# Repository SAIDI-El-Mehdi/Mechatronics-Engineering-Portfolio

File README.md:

# Mechatronics-Engineering-Portfolio
Academic projects and labs at ENSA Agadir.

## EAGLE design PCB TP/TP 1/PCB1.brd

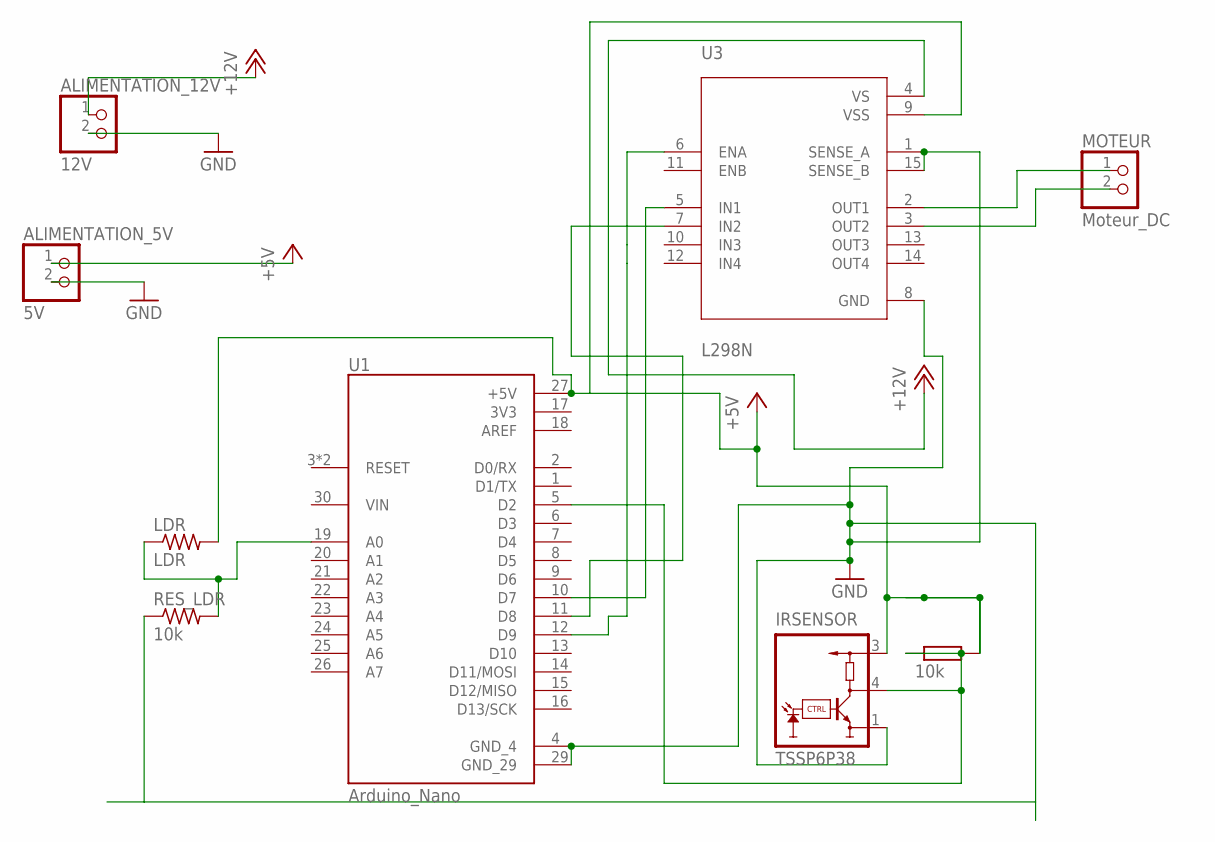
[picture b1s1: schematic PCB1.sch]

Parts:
ALIMENTATION_5V: 5V; 1X02
ALIMENTATION_12V: 12V; 1X02
IRSENSOR: TSSP6P38
LDR: LDR; WSC01/2
MOTEUR: Moteur_DC; 1X02
RES_LDR: 10k; 0204/5
R_PULL_UP: 10k; 0204V
U1: Arduino_Nano; MODULE_ARDUINO_NANO
U3: L298N; TO127P2020X500X2100-15

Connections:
+5V: ALIMENTATION_5V.1, IRSENSOR.3 (VS), LDR.2, R_PULL_UP.2, U1.27 (+5V), U3.9 (VSS)
+12V: ALIMENTATION_12V.1, U3.4 (VS)
GND: ALIMENTATION_5V.2, ALIMENTATION_12V.2, IRSENSOR.1 (GND), RES_LDR.1, U1.4 (GND_4), U1.29 (GND_29), U3.1 (SENSE_A), U3.8 (GND), U3.15 (SENSE_B)
IR_OUT: IRSENSOR.4 (OUT), R_PULL_UP.1, U1.5 (D2)
L298_ENA: U1.12 (D9), U3.6 (ENA)
L298_IN1: U1.10 (D7), U3.5 (IN1)
L298_IN2: U1.11 (D8), U3.7 (IN2)
LDR_SIGNAL: LDR.1, RES_LDR.2, U1.19 (A0)
MOTOR_OUT1: MOTEUR.1, U3.2 (OUT1)
MOTOR_OUT2: MOTEUR.2, U3.3 (OUT2)

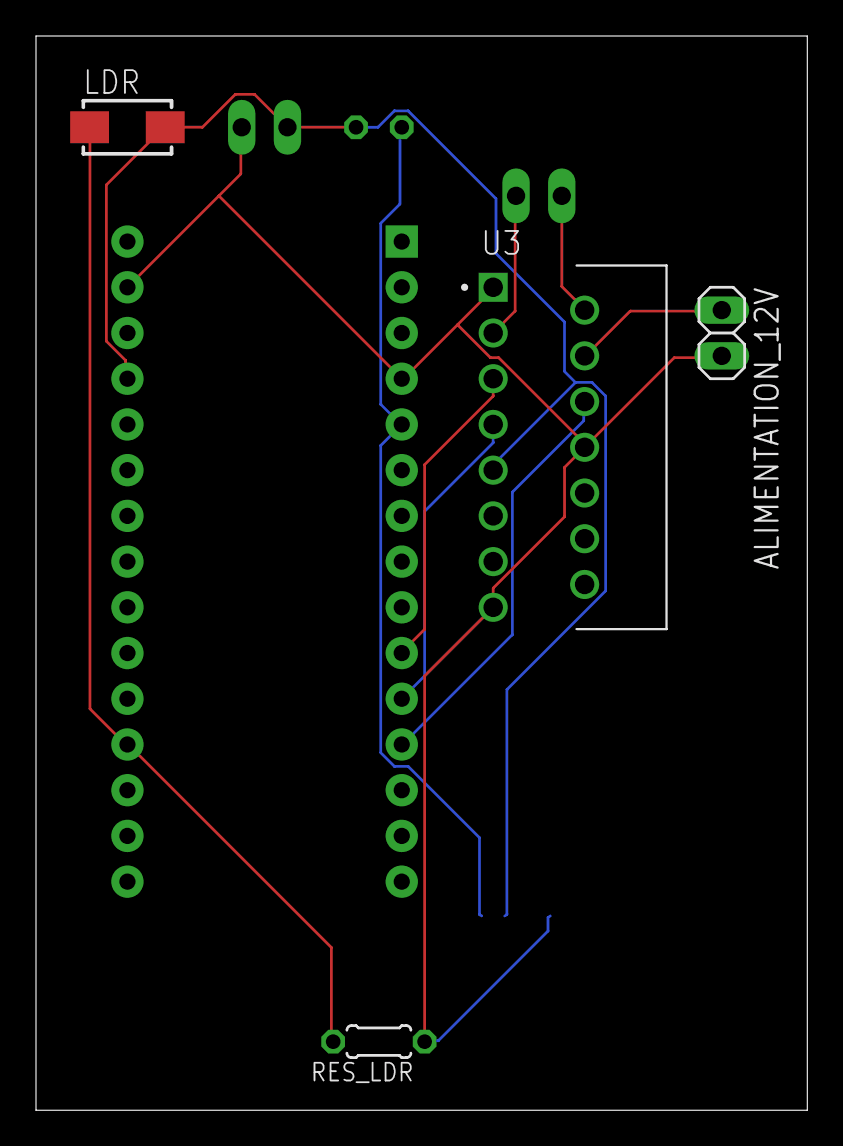
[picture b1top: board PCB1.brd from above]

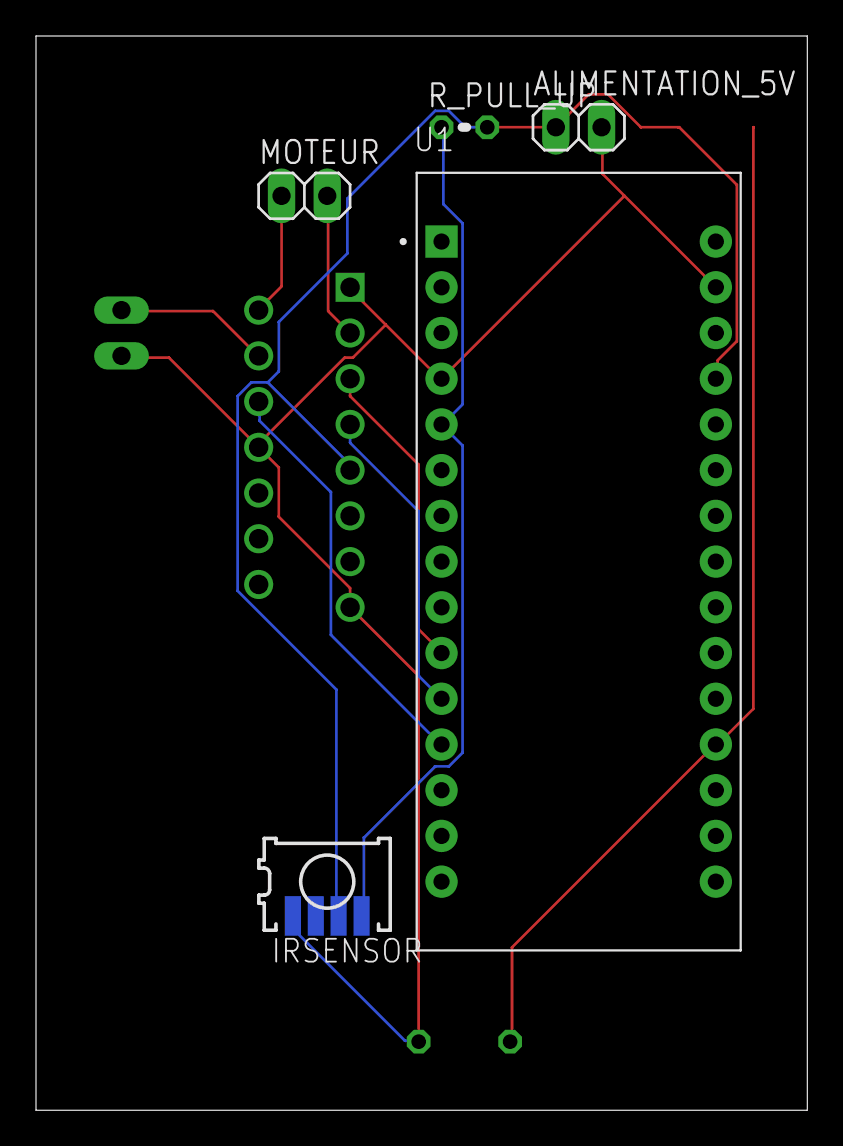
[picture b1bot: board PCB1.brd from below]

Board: 2 copper layers, 42.9 x 59.7 mm, 9 parts (5 on the bottom side), 10 nets.

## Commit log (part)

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2025-12-16 Create README.md
    Projects for Embedded Systems
2025-12-16 Create README.md
    Smart Traffic Light Controller (VHDL)
    Implemented on FPGA (Cyclone/Altera) using VHDL.
    Features:
    - Finite State Machine (FSM) for traffic logic.
    - Automatic and Manual modes.
2025-12-16 Add VHDL Smart Traffic Light Controller
    Uploaded structural architecture files, testbench, and Quartus project settings.
2025-12-16 Create README.md
    3-to-8 LED Decoder (VHDL)
    Simple combinatorial logic to control 8 LEDs using 3 switches (Case statement).
2025-12-16 Add VHDL code for 3-to-8 Decoder
    LED-Decoder-3to8
2025-12-16 Create README.md
    4-Bit Binary Adder with 7-Segment Display
    Structural VHDL implementation of a 4-bit Full Adder using 1-bit adder components.
    Features:
    - 4-bit addition using structural architecture.
    - Binary to BCD conversion.
    - Output display on 7-Segment HEX (Units and Tens).
2025-12-16 Add structural 4-bit adder with BCD display
2025-12-16 Create README.md
    Modulo-N Counter with 7-Segment Display
    A flexible counter that counts up to a user-defined value 'N'.
    Features:
    - User-defined Modulo limit (input N).
    - Clock Divider for visible counting speed (1Hz approx).
    - Dynamic display on 7-Segment HEX displays.
2025-12-16 dd Modulo-N counter with display controller
2025-12-16 Create README.md
    # Gear Train Mechanism (DMU Kinematics)
    3D Modeling and Kinematic simulation of a gear train system using CATIA V5.
    ## 📸 Design Preview
    ![Gear Assembly Render](./render_gears.png)
    ## ⚙️ Features
    - Parametric gear design.
2025-12-16 Gear-Train-DMU.
2025-12-16 Create README.md
    # Scotch Yoke Mechanism (Transformation de Mouvement)
    A kinematic simulation of a Scotch Yoke mechanism designed in CATIA V5.
    This mechanism converts rotational motion into linear reciprocating motion.
    ## 📸 Project Gallery
    Here is the 3D Isometric view and the Assembly Tree structure:
    ![3D Render](./render_iso.png)
2025-12-16 Scotch-Yoke-Mechanism
    # Scotch Yoke Mechanism (Transformation de Mouvement)
    A kinematic simulation of a Scotch Yoke mechanism designed in CATIA V5.
    This mechanism converts rotational motion into linear reciprocating motion.
    ## 📸 Project Gallery
    Here is the 3D Isometric view and the Assembly Tree structure:
    ![3D Render](./render_iso.png)
2025-12-16 Update README.md
    ## 📸 Project Gallery
    Here is the 3D Isometric view and the Assembly Tree structure:
    ![3D Render](./render_iso.png.jpg)
    ![Design Tree](./design_tree.jpg.png)
2025-12-16 Axe-Galet-Assembly
2025-12-16 Create README.md
    # Agricultural Tractor Design (Tracteur Agricole)
    A detailed 3D model of an agricultural tractor designed in CATIA V5.
    This project demonstrates complex **Part Design** and multi-body modeling techniques.
    ## 📸 Design Views
    Here are the Isometric, Top, Side, and Front views of the tractor:
    ![Tractor Views](./tractor_views.jpg)
2025-12-16 TRACTOR.CATPart
2025-12-16 Create README.md
    # Asynchronous Motor Design (Moteur Asynchrone)
    3D Modeling of an industrial Asynchronous Induction Motor using CATIA V5.
    Focus on external housing details and cooling system design.
    ## 📸 Motor Views
    Detailed view of the housing, cooling fins, and terminal box:
    ![Motor Views](./motor_views.jpg)
2025-12-16 Asynchronous-Motor-Design
2025-12-16 Rename folders
2025-12-16 Create README.md
    # Artificial Respirator Mechanism (Respirateur Artificiel)
    Design of a mechanical ventilator system intended for emergency respiratory support.
    The mechanism converts rotary motion from a DC motor into a linear compression stroke to actuate an Ambu bag.
    ## 📸 Assembly Views
    Simulation of the compression mechanism:
    ![Respirator Assembly](./respirator_views.jpg)
2025-12-16 Artificial-Respirator
2025-12-16 Weather-App
2025-12-21 Create Matlab-Simulink-Control
2025-12-21 Matlab-Simulink-Control
2025-12-28 Create Autonomous-Vehicle-Path-Tracking
2025-12-28 Autonomous-Vehicle-Path-Tracking
    Initial upload of the Autonomous Vehicle Path Tracking project.
    Included files:
    - AEB_Project.slx: The main Simulink model implementing the 3DOF vehicle dynamics and Pure Pursuit controller.
    - PathPlanning_Step1.m: MATLAB initialization script for generating the reference path and setting vehicle parameters.
    - path_tracking_result_final.png.png: Simulation result showing the comparison between the planned path and the actual vehicle trajectory.
2025-12-28 Numerical-Analysis-Algorithms
    Implementation of fundamental Numerical Analysis algorithms using MATLAB.
    This collection includes:
    - Newton.m: Newton-Raphson method for finding roots of non-linear equations.
    - RK4.m: Runge-Kutta 4th Order method for solving Ordinary Differential Equations (ODEs).
    - Lagrange.m: Polynomial interpolation for data fitting.
    - Resolution.m: Algorithm for solving systems of linear equations (Ax=B).
2025-12-28 TrafficLight_Project.qpf
2025-12-28 tb_TrafficLight.vhd
2025-12-28 TrafficLight_Sim_Model.vhd
2025-12-28 TrafficLight_Top.vhd
2025-12-28 Adder4Bit_Project.qpf
2025-12-28 tb_Adder4Bit.vhd
2025-12-31 Update README.md
    Upgrade: Added safety logic for autonomous stop and improved path tracking accuracy
2025-12-31 Create path_tracking_model
2025-12-31 Autonomous-Vehicle-Project
2025-12-31 README.md
2025-12-31 Rename Final_Result_Plot+Simulink_Diagram.png to Final_Result_Plot.png
2026-03-08 👉 Add VHDL Sensor Project core files
    👉 Uploaded the main VHDL design (Sensor_Project.vhd), the Quartus project configuration (.qpf), and the testbench file for the digital sensor interface on Altera DE0.
2026-03-11 VGA controller VHDL core file
    Uploaded the main VHDL logic (12.vhd), Quartus configuration, and description for the VGA display controller on Altera DE0
2026-03-11 Add Nios II HW/SW Co-design project files
    Uploaded top-level VHDL (Projet3_Nios.vhd), Qsys processor architecture (nios_system.qsys), Quartus configurations, and the C application code for DE0 board.
